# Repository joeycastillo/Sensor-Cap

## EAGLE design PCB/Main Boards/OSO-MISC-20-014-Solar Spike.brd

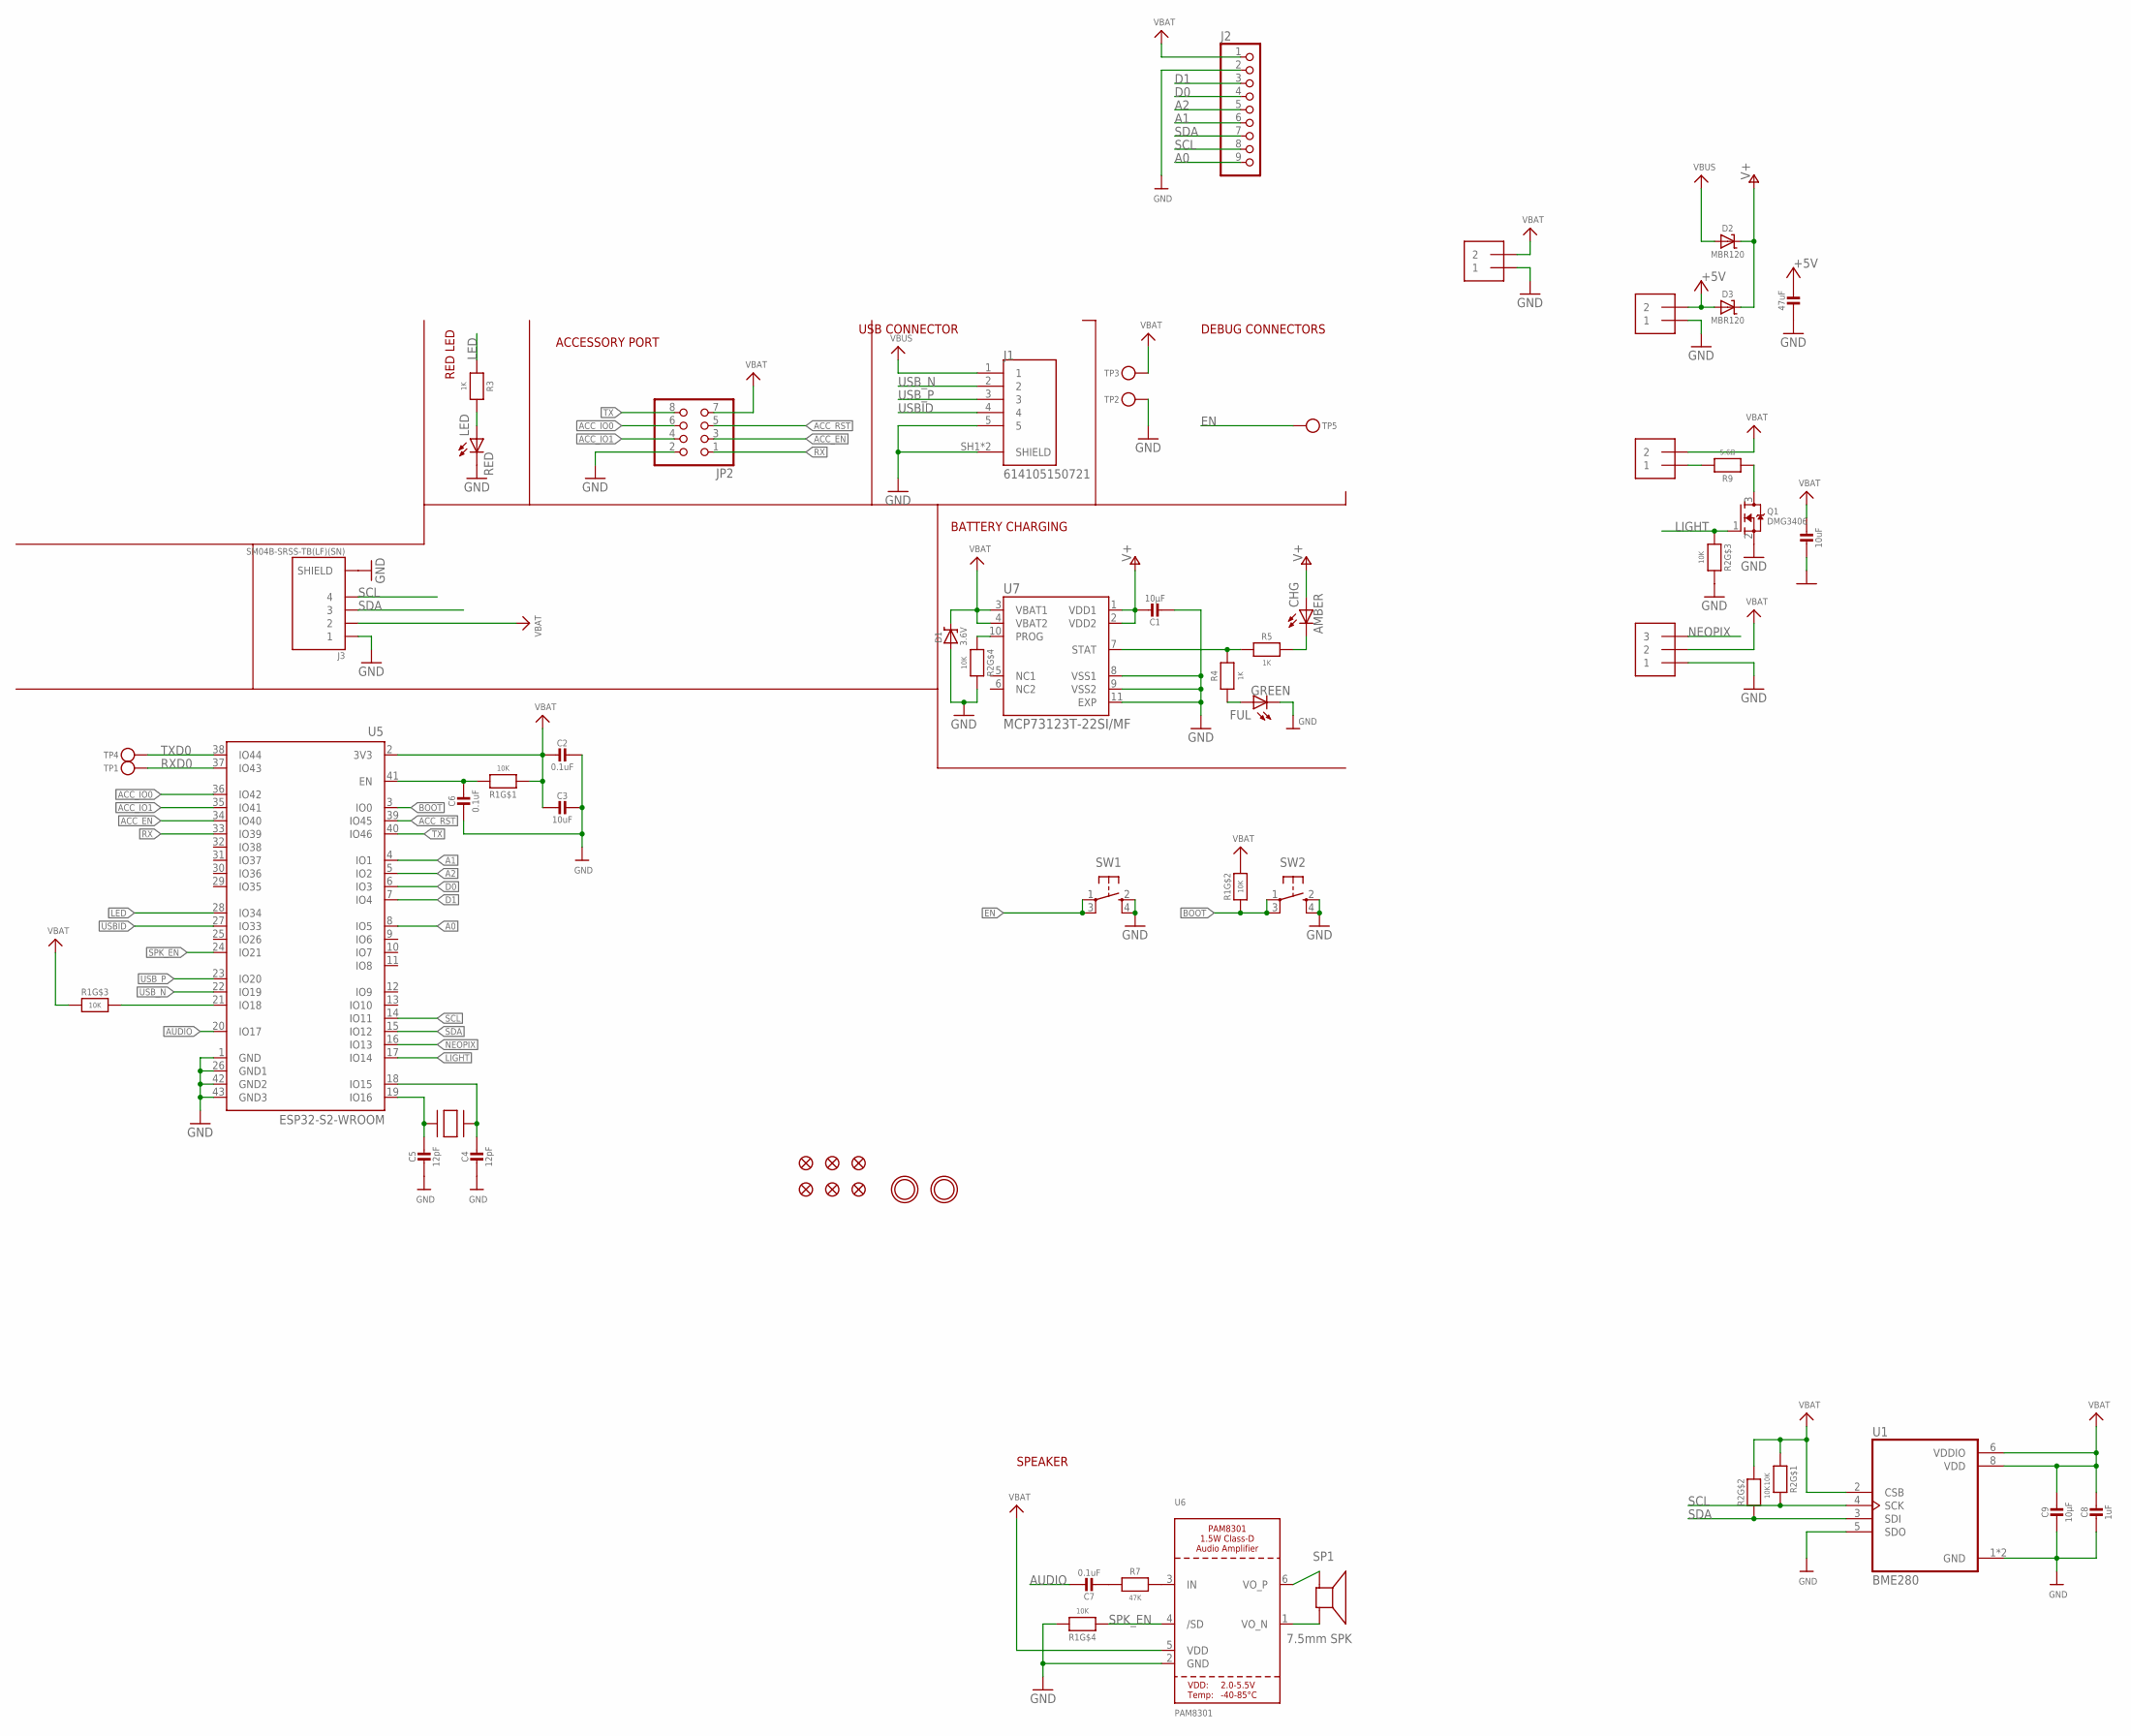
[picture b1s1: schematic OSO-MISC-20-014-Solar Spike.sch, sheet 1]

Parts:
BATTERY: 1X2-3.5MM
C1, C9: 10µF; 0805-NO
C2, C6, C7: 0.1uF; 0805-NO
C3, C10: 10uF; 0805-NO
C4, C5: 12pF; 0805-NO
C8: 1uF; 0805-NO
C11: 47uF; 0805-NO
CHG: AMBER; CHIPLED_0805
D1: 3.6V; SOD-123
D2, D3: MBR120; SOD-123
FID1, FID2, FID3, FID4, FID5, FID6: FIDUCIAL_1MM
FUL: GREEN; CHIPLED_0805
J1: 614105150721; WURTH_614105150721
J2: HEADER-1X9_JSTSH_VERT; JST_SH9_VERT
J3: SM04B-SRSS-TB(LF)(SN); JST_SM04B-SRSS-TB(LF)(SN)
JP2: PINHD-2X4SMT; PINHD_2X4_SMT
LED: RED; CHIPLED_0805
LIGHT: 1X2-3.5MM
NEOPIX: 1X3; 1X3-3.5MM
Q1: DMG3406; SOT23-WIDE
R1, R2: 10K; EXBV8V
R3, R4, R5: 1K; 0805-NO
R7: 47K; 0805-NO
R9: 5.6Ω; 0805-NO
SOLAR: 1X2-3.5MM
SP1: 7.5mm SPK; BUZZER_SMT_5MM
SW1, SW2: SPST_TACT-KMR2; KMR2
TP1, TP2, TP3, TP4, TP5: TESTPOINTROUND1.5MMNO; TESTPOINT_ROUND_1.5MM_NO
U1: BME280; PSON65P250X250X100-8N
U5: ESP32-S2-WROOM; MODULE_ESP32-S2-WROOM
U6: PAM8301; SOT23-6
U7: MCP73123T-22SI/MF; SON50P300X300X100-11N
U$1, U$4: MOUNTINGHOLE2.5; MOUNTINGHOLE_2.5_PLATED
X1: XTAL-3.2X1.5; XTAL3215

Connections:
+5V: C11.2, D3.A, SOLAR.2
A0: J2.9, U5.8 (IO5)
A1: J2.6, U5.4 (IO1)
A2: J2.5, U5.5 (IO2)
ACC_EN: JP2.3, U5.34 (IO40)
ACC_IO0: JP2.6, U5.36 (IO42)
ACC_IO1: JP2.4, U5.35 (IO41)
ACC_RST: JP2.5, U5.39 (IO45)
AUDIO: C7.1, U5.20 (IO17)
BOOT: R1.2 (1), SW2.1, SW2.3 (P1), U5.3 (IO0)
D0: J2.4, U5.6 (IO3)
D1: J2.3, U5.7 (IO4)
EN: C6.1, R1.8 (2), SW1.1, SW1.3 (P1), TP5.P$1, U5.41 (EN)
GND: BATTERY.1, C1.2, C2.1, C3.1, C4.2, C5.2, C6.2, C8.2, C9.2, C10.2, C11.1, D1.A, FUL.C, J1.5, J1.SH1 (SHIELD), J1.SH2 (SHIELD), J2.2, J3.1, J3.S1 (SHIELD), J3.S2 (SHIELD), JP2.2, LED.C, NEOPIX.1, Q1.2 (S), R1.5 (2), R2.5 (2), R2.6 (2), SOLAR.1, SW1.2 (S), SW1.4 (S1), SW2.2 (S), SW2.4 (S1), TP2.P$1, U1.1 (GND), U1.5 (SDO), U1.7 (GND), U5.1 (GND), U5.26 (GND1), U5.42 (GND2), U5.43 (GND3), U6.2 (GND), U7.8 (VSS1), U7.9 (VSS2), U7.11 (EXP)
LED: R3.1, U5.28 (IO34)
LIGHT: Q1.1 (G), R2.3 (1), U5.17 (IO14)
unnamed: R1.6 (2), U5.21 (IO18)
unnamed: LED.A, R3.2
unnamed: C7.2, R7.1
unnamed: R7.2, U6.3 (IN)
unnamed: CHG.C, R5.2
unnamed: FUL.A, R4.1
unnamed: Q1.3 (D), R9.1
unnamed: LIGHT.1, R9.2
NEOPIX: NEOPIX.3, U5.16 (IO13)
PROG: R2.4 (1), U7.10 (PROG)
RX: JP2.1, U5.33 (IO39)
RXD0: TP1.P$1, U5.37 (IO43)
SCL: J2.8, J3.4, R2.8 (2), U1.4 (SCK), U5.14 (IO11)
SDA: J2.7, J3.3, R2.7 (2), U1.3 (SDI), U5.15 (IO12)
SPK_EN: R1.4 (1), U5.24 (IO21), U6.4 (/SD)
SPK_N: SP1.+, U6.1 (VO_N)
SPK_P: SP1.-, U6.6 (VO_P)
STAT: R4.2, R5.1, U7.7 (STAT)
TX: JP2.8, U5.40 (IO46)
TXD0: TP4.P$1, U5.38 (IO44)
USBID: J1.4, U5.27 (IO33)
USB_N: J1.2, U5.22 (IO19)
USB_P: J1.3, U5.23 (IO20)
V+: C1.1, CHG.A, D2.C, D3.C, U7.1 (VDD1), U7.2 (VDD2)
VBAT: BATTERY.2, C2.2, C3.2, C8.1, C9.1, C10.1, D1.C, J2.1, J3.2, JP2.7, LIGHT.2, NEOPIX.2, R1.1, R1.3 (1), R1.7 (2), R2.1, R2.2 (1), TP3.P$1, U1.2 (CSB), U1.6 (VDDIO), U1.8 (VDD), U5.2 (3V3), U6.5 (VDD), U7.3 (VBAT1), U7.4 (VBAT2)
VBUS: D2.A, J1.1
XTAL_N: C5.1, U5.19 (IO16), X1.P$2
XTAL_P: C4.1, U5.18 (IO15), X1.P$1

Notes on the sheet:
BATTERY CHARGING
DEBUG CONNECTORS
USB CONNECTOR
RED LED
SPEAKER
ACCESSORY PORT

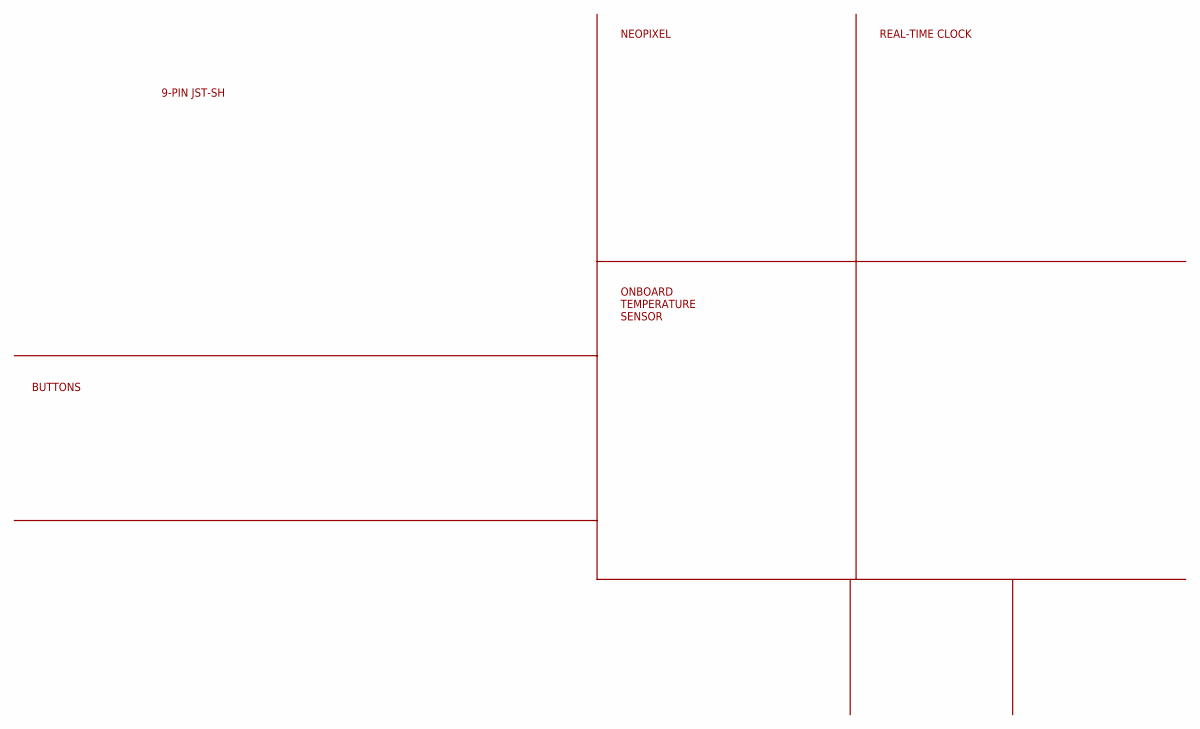
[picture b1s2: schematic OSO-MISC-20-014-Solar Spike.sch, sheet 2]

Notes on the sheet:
9-PIN JST-SH
ONBOARD TEMPERATURE SENSOR
BUTTONS
NEOPIXEL
REAL-TIME CLOCK

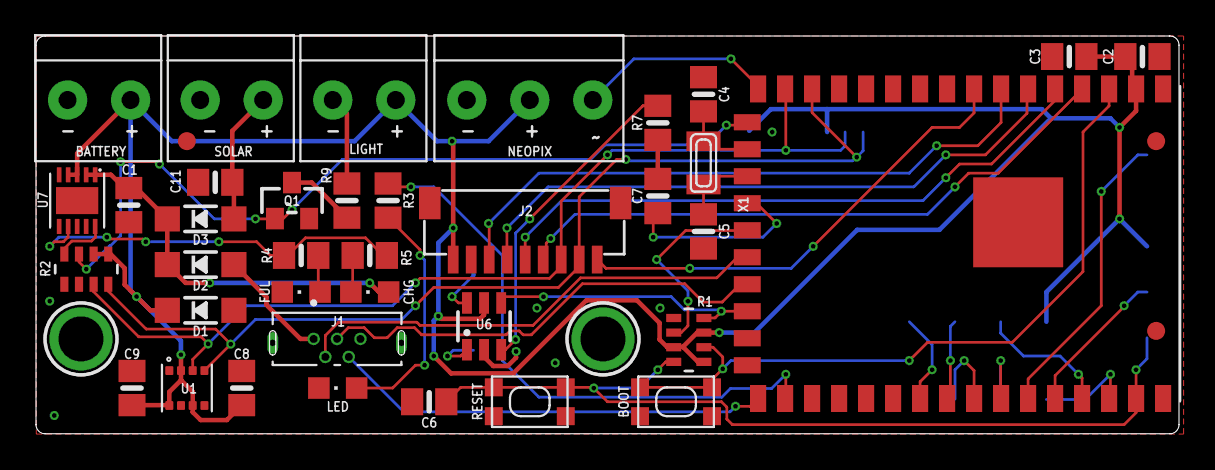
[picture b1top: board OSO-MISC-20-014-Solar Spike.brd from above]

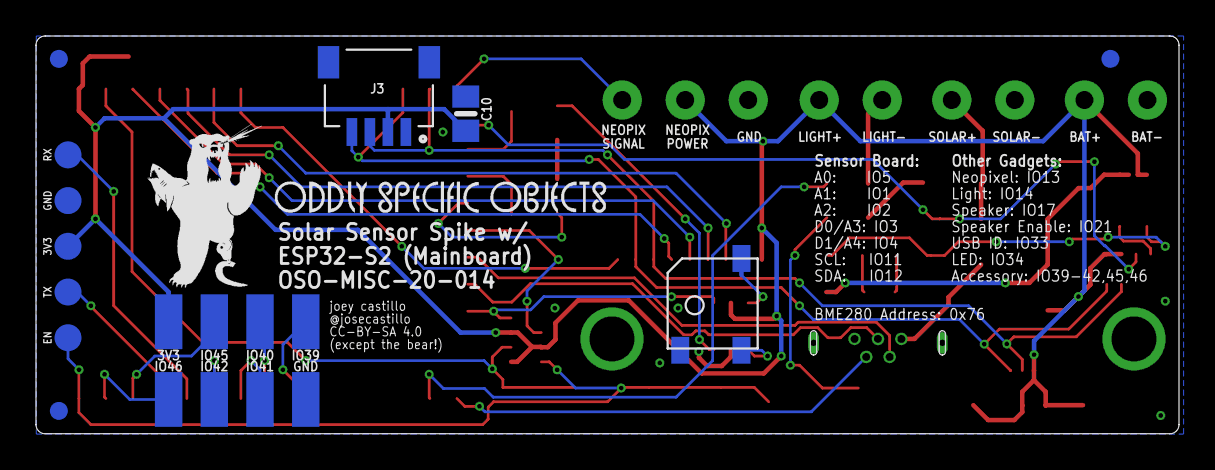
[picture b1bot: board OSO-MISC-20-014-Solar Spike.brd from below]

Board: 2 copper layers, 63.5 x 22.1 mm, 56 parts (14 on the bottom side), 44 nets.

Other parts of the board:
U$15: OSO_BEAR_250X360MIL_1000DPI
U$31: OSO_WORDMARK_ONELINE_725MIL_1000DPI

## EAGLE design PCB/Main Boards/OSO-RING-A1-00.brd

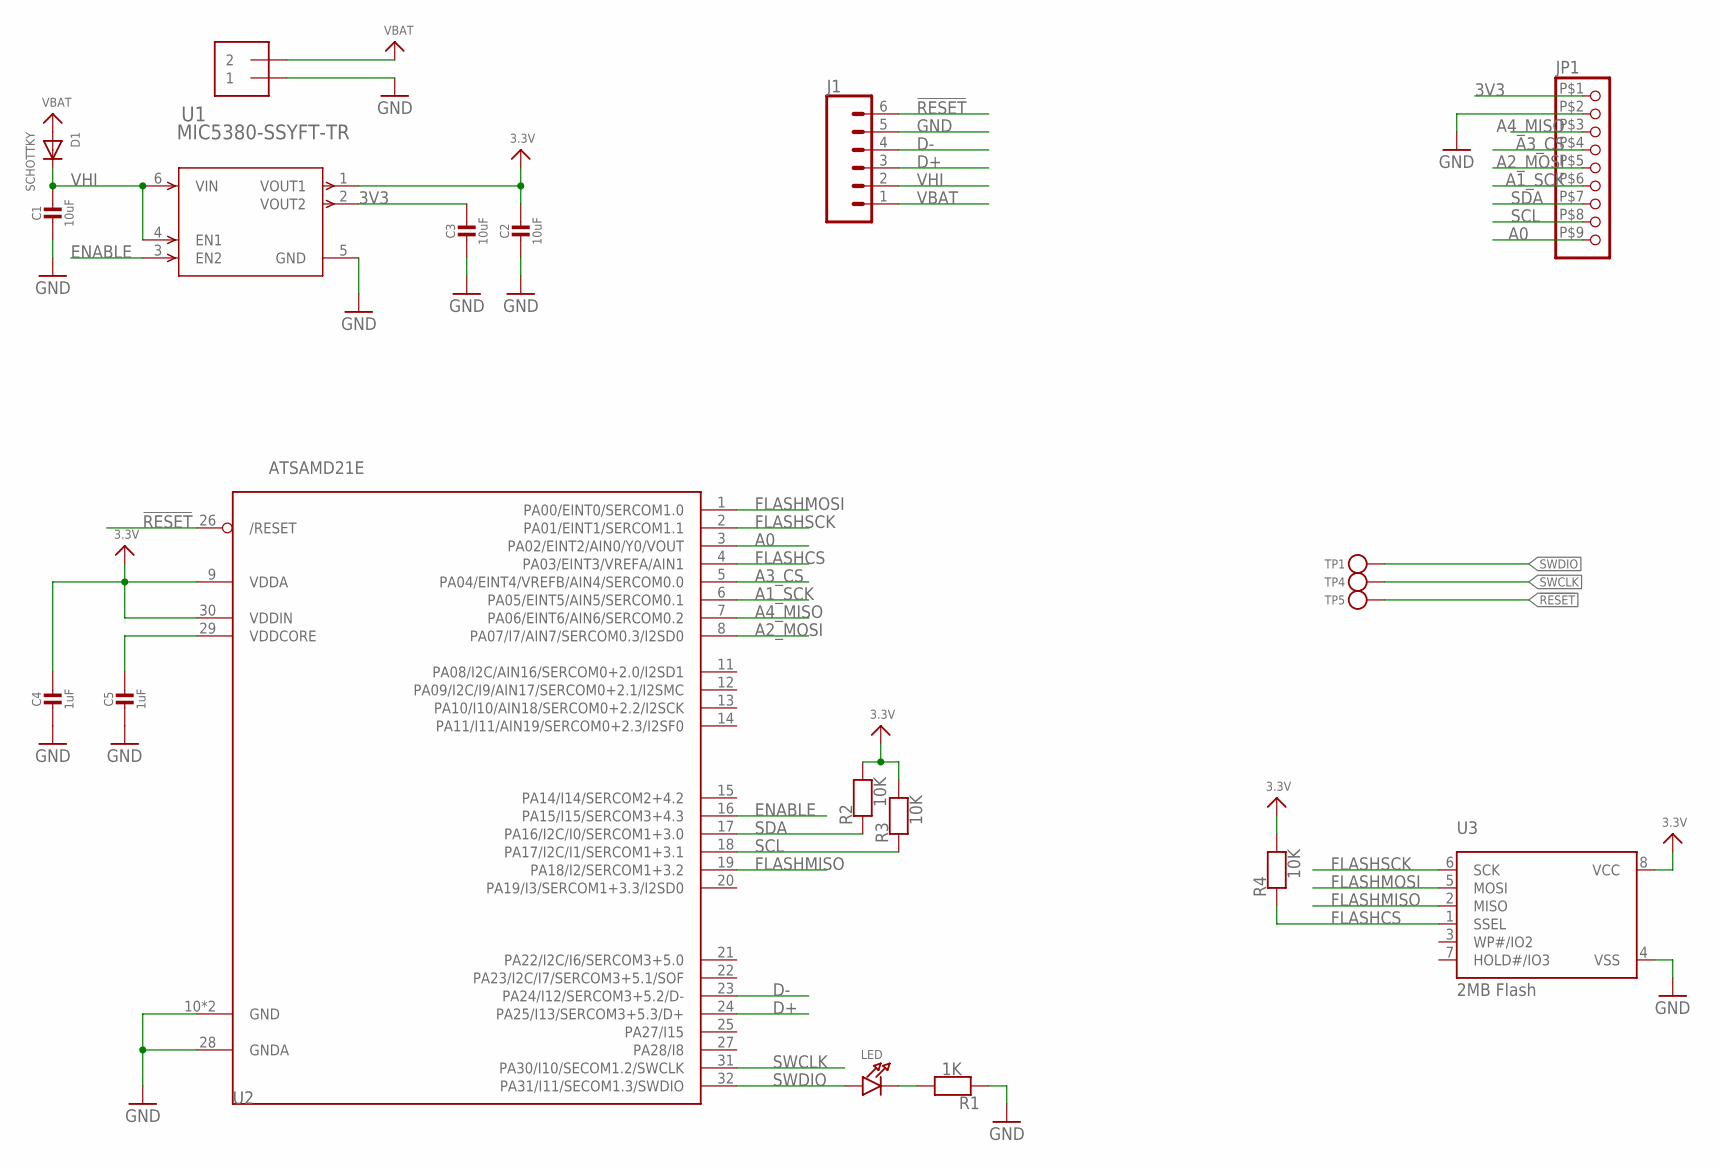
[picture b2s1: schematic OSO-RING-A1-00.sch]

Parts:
C1, C2, C3: 10uF; 0603-NO
C4, C5: 1uF; 0603-NO
D1: SCHOTTKY; SOD-123
J1: CONN_06SMD-1MM; 1X06-1MM
J2: 1X2SMT; 2PIN_SMT_CONNECTOR
JP1: HEADER-1X9BOARD_TO_FLEX; 9PIN_SMT_CONNECTOR
LED: LED0603_NOOUTLINE; CHIPLED_0603_NOOUTLINE
R1: 1K; 0603-NO
R2, R3, R4: 10K; 0603-NO
TP1, TP4, TP5: TESTPOINTROUND1.5MMNO; TESTPOINT_ROUND_1.5MM_NO
U1: MIC5380-SSYFT-TR; TMLF-6_FT_MCH
U2: ATSAMD21E; QFN32_5MM
U3: 2MB Flash; USON8

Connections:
3.3V: C2.1, C4.1, R2.2, R3.2, R4.2, U1.1 (VOUT1), U2.9 (VDDA), U2.30 (VDDIN), U3.8 (VCC)
3V3: C3.1, JP1.P$1 (1), U1.2 (VOUT2)
!RESET: J1.6, TP5.P$1, U2.26 (/RESET)
A0: JP1.P$9 (9), U2.3 (PA02/EINT2/AIN0/Y0/VOUT)
A1_SCK: JP1.P$6 (6), U2.6 (PA05/EINT5/AIN5/SERCOM0.1)
A2_MOSI: JP1.P$5 (5), U2.8 (PA07/I7/AIN7/SERCOM0.3/I2SD0)
A3_CS: JP1.P$4 (4), U2.5 (PA04/EINT4/VREFB/AIN4/SERCOM0.0)
A4_MISO: JP1.P$3 (3), U2.7 (PA06/EINT6/AIN6/SERCOM0.2)
D+: J1.3, U2.24 (PA25/I13/SERCOM3+5.3/D+)
D-: J1.4, U2.23 (PA24/I12/SERCOM3+5.2/D-)
ENABLE: U1.3 (EN2), U2.16 (PA15/I15/SERCOM3+4.3)
FLASHCS: R4.1, U2.4 (PA03/EINT3/VREFA/AIN1), U3.1 (SSEL)
FLASHMISO: U2.19 (PA18/I2/SERCOM1+3.2), U3.2 (MISO)
FLASHMOSI: U2.1 (PA00/EINT0/SERCOM1.0), U3.5 (MOSI)
FLASHSCK: U2.2 (PA01/EINT1/SERCOM1.1), U3.6 (SCK)
GND: C1.2, C2.2, C3.2, C4.2, C5.2, J1.5, J2.P$1 (1), JP1.P$2 (2), R1.1, U1.5 (GND), U2.10 (GND), U2.28 (GNDA), U2.33 (GND), U3.4 (VSS)
unnamed: LED.C, R1.2
SCL: JP1.P$8 (8), R3.1, U2.18 (PA17/I2C/I1/SERCOM1+3.1)
SDA: JP1.P$7 (7), R2.1, U2.17 (PA16/I2C/I0/SERCOM1+3.0)
SWCLK: TP4.P$1, U2.31 (PA30/I10/SECOM1.2/SWCLK)
SWDIO: LED.A, TP1.P$1, U2.32 (PA31/I11/SECOM1.3/SWDIO)
VBAT: D1.A, J1.1, J2.P$2 (2)
VDDCORE: C5.1, U2.29 (VDDCORE)
VHI: C1.1, D1.C, J1.2, U1.4 (EN1), U1.6 (VIN)

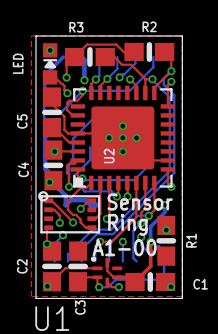
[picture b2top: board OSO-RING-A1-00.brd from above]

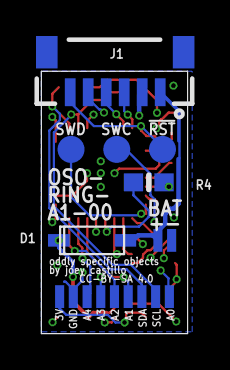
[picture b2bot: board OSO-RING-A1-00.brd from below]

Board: 4 copper layers, 8.1 x 14.6 mm, 20 parts (8 on the bottom side), 24 nets.

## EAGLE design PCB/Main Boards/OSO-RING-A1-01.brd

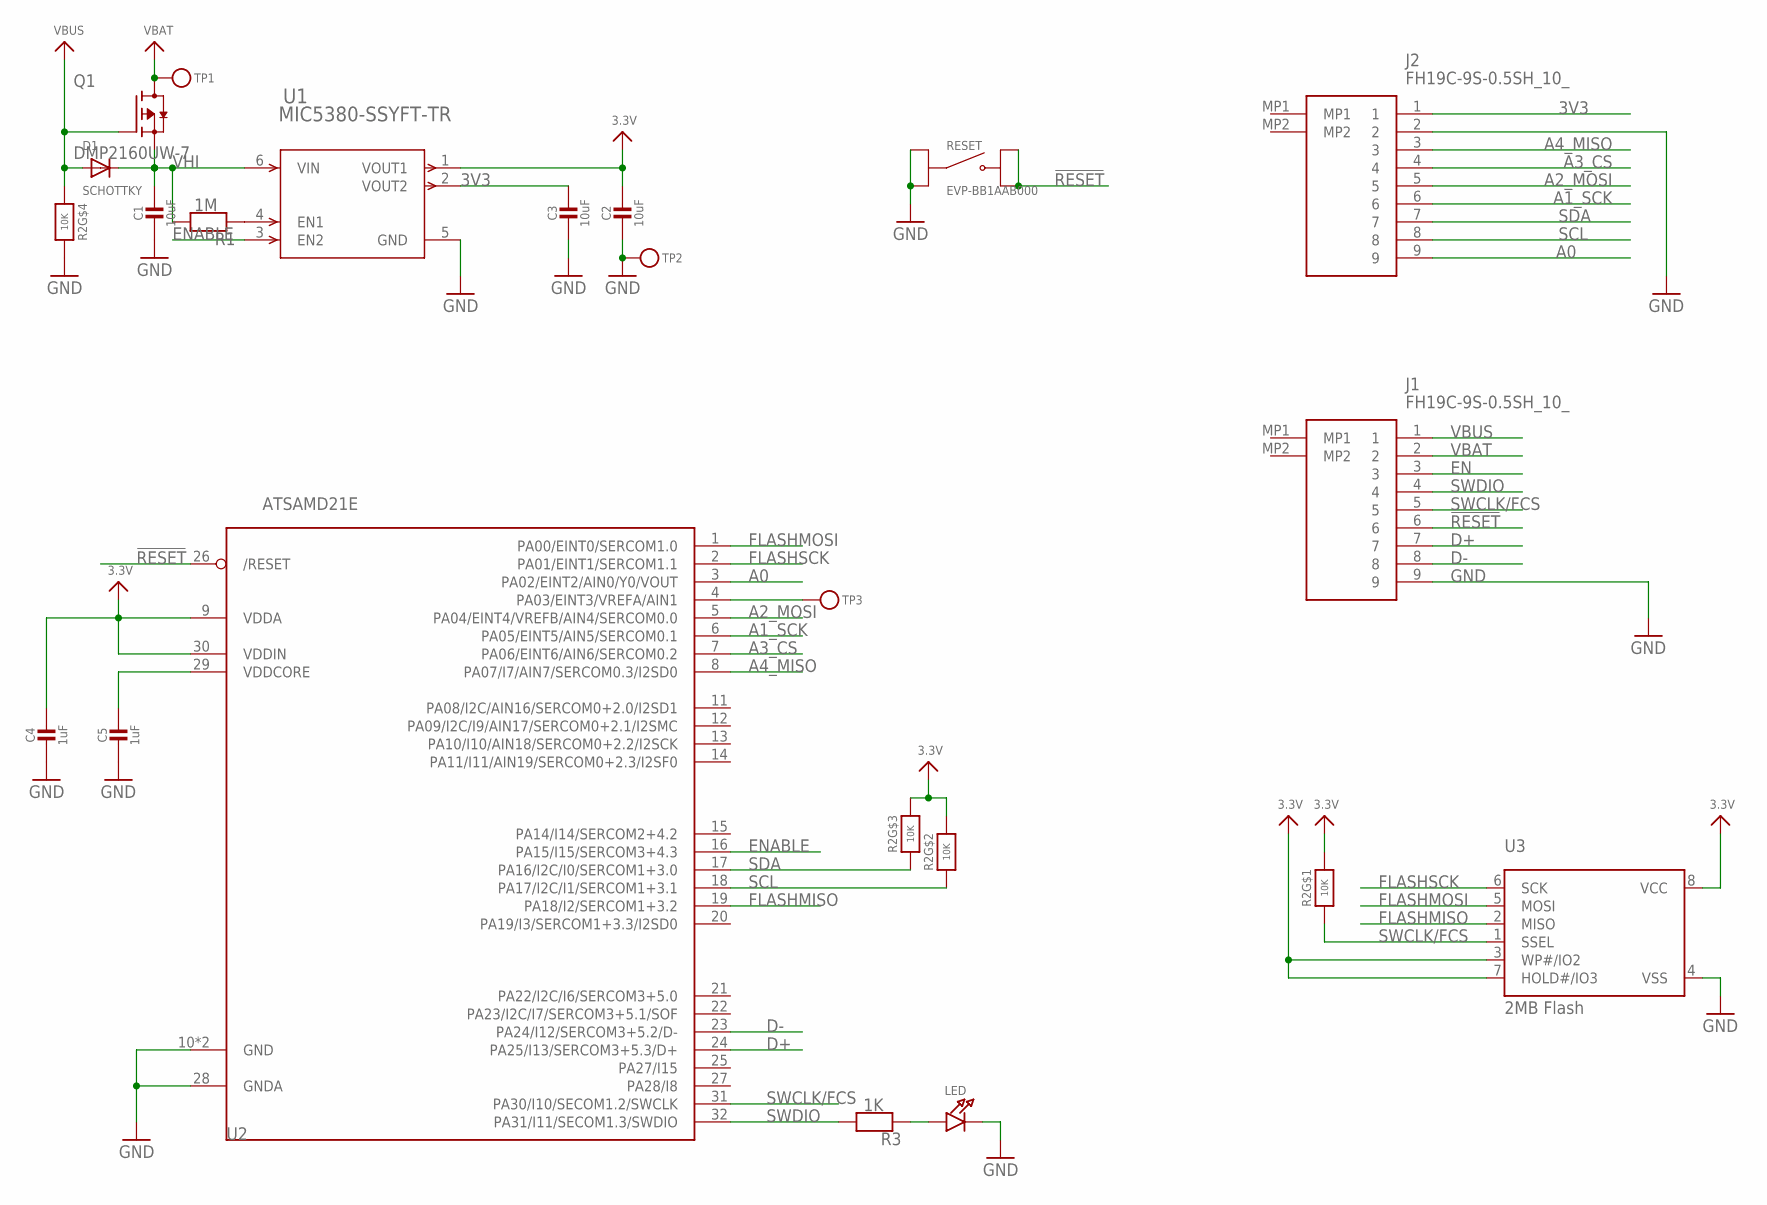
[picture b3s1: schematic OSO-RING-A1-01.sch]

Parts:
C1, C2, C3: 10uF; _0603MP
C4, C5: 1uF; _0603MP
D1: SCHOTTKY; SOD-323F
J1, J2: FH19C-9S-0.5SH_10_; FH19C9S05SH10
LED: LED0603_NOOUTLINE; CHIPLED_0603_NOOUTLINE
Q1: DMP2160UW-7; SOT65P210X110-3N
R1: 1M; _0603MP
R2: 10K; EXBV8V
R3: 1K; _0603MP
RESET: EVP-BB1AAB000; SW_EVP-BB1AAB000
TP1, TP2: TESTPOINTPAD2MM; TESTPOINT_PAD_2MM
TP3: TESTPOINTPAD1MM; TESTPOINT_PAD_1MM
U1: MIC5380-SSYFT-TR; TMLF-6_FT_MCH
U2: ATSAMD21E; QFN32_5MM
U3: 2MB Flash; USON8

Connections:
3.3V: C2.1, C4.1, R2.6 (2), R2.7 (2), R2.8 (2), U1.1 (VOUT1), U2.9 (VDDA), U2.30 (VDDIN), U3.3 (WP#/IO2), U3.7 (HOLD#/IO3), U3.8 (VCC)
3V3: C3.1, J2.1, U1.2 (VOUT2)
!RESET: J1.6, RESET.B1, RESET.B2, U2.26 (/RESET)
A0: J2.9, U2.3 (PA02/EINT2/AIN0/Y0/VOUT)
A1_SCK: J2.6, U2.6 (PA05/EINT5/AIN5/SERCOM0.1)
A2_MOSI: J2.5, U2.5 (PA04/EINT4/VREFB/AIN4/SERCOM0.0)
A3_CS: J2.4, U2.7 (PA06/EINT6/AIN6/SERCOM0.2)
A4_MISO: J2.3, U2.8 (PA07/I7/AIN7/SERCOM0.3/I2SD0)
D+: J1.7, U2.24 (PA25/I13/SERCOM3+5.3/D+)
D-: J1.8, U2.23 (PA24/I12/SERCOM3+5.2/D-)
EN: J1.3, R1.1, U1.4 (EN1)
ENABLE: U1.3 (EN2), U2.16 (PA15/I15/SERCOM3+4.3)
FLASHMISO: U2.19 (PA18/I2/SERCOM1+3.2), U3.2 (MISO)
FLASHMOSI: U2.1 (PA00/EINT0/SERCOM1.0), U3.5 (MOSI)
FLASHSCK: U2.2 (PA01/EINT1/SERCOM1.1), U3.6 (SCK)
FREE_PIN!: TP3.P$1, U2.4 (PA03/EINT3/VREFA/AIN1)
GND: C1.2, C2.2, C3.2, C4.2, C5.2, J1.9, J2.2, LED.C, R2.5 (2), RESET.A1, RESET.A2, TP2.P$1, U1.5 (GND), U2.10 (GND), U2.28 (GNDA), U2.33 (GND), U3.4 (VSS)
unnamed: LED.A, R3.1
SCL: J2.8, R2.2 (1), U2.18 (PA17/I2C/I1/SERCOM1+3.1)
SDA: J2.7, R2.3 (1), U2.17 (PA16/I2C/I0/SERCOM1+3.0)
SWCLK/FCS: J1.5, R2.1, U2.31 (PA30/I10/SECOM1.2/SWCLK), U3.1 (SSEL)
SWDIO: J1.4, R3.2, U2.32 (PA31/I11/SECOM1.3/SWDIO)
VBAT: J1.2, Q1.3 (D), TP1.P$1
VBUS: D1.A, J1.1, Q1.1 (G), R2.4 (1)
VDDCORE: C5.1, U2.29 (VDDCORE)
VHI: C1.1, D1.C, Q1.2 (S), R1.2, U1.6 (VIN)

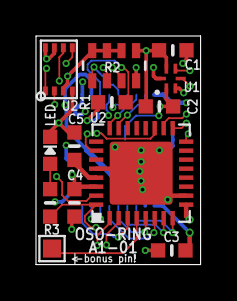
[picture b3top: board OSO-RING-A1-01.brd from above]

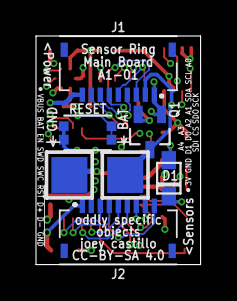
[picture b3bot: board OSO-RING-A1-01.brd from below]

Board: 6 copper layers, 9.1 x 12.7 mm, 20 parts (7 on the bottom side), 26 nets.

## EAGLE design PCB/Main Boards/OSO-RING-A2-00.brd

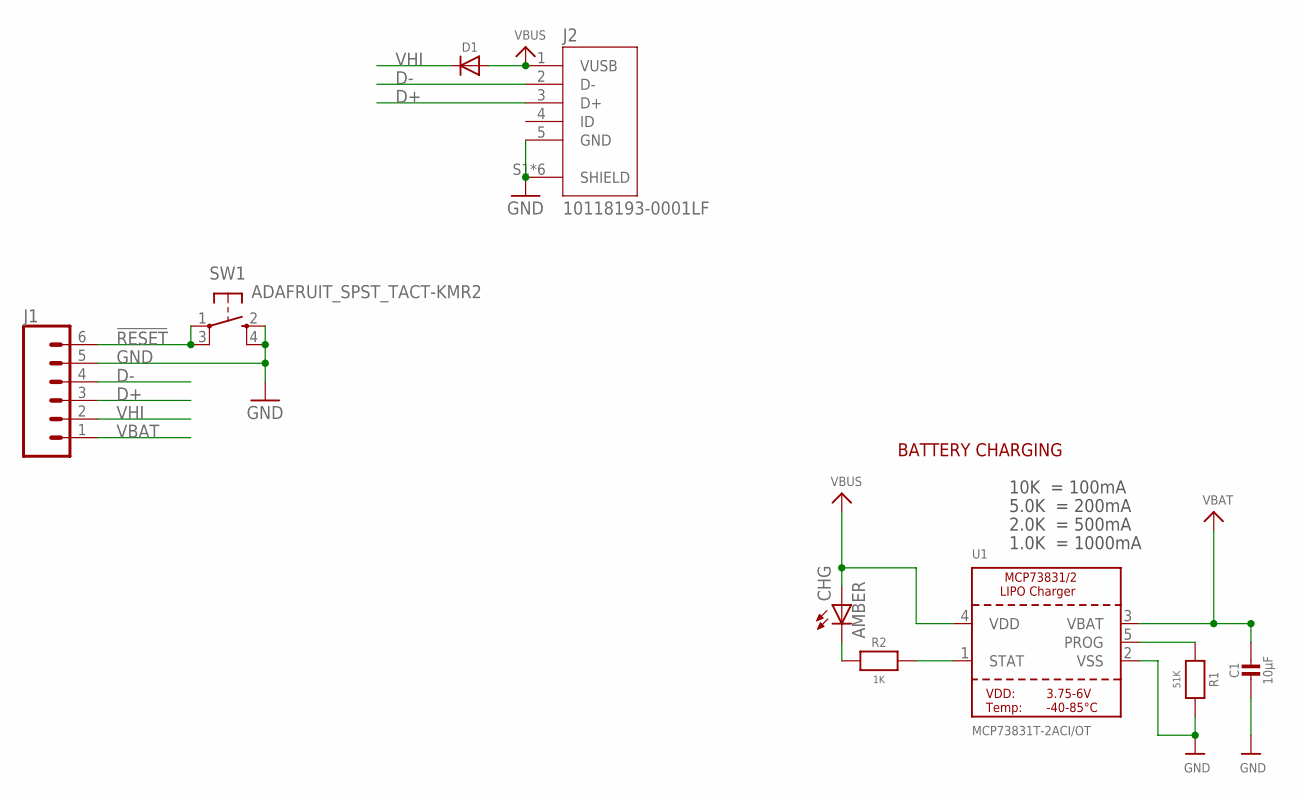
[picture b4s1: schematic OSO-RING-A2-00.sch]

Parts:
C1: 10µF; 0805-NO
CHG: AMBER; CHIPLED_0805
D1: MICROBUILDER_DIODESOD-123; MICROBUILDER_SOD-123
J1: CONN_06SMD-1MM; 1X06-1MM
J2: 10118193-0001LF; FCI_10118193-0001LF
R1: 51K; 0805-NO
R2: 1K; 0805-NO
SW1: ADAFRUIT_SPST_TACT-KMR2; ADAFRUIT_KMR2
U1: MCP73831T-2ACI/OT; SOT23-5

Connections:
!RESET: J1.6, SW1.1, SW1.3 (P1)
D+: J1.3, J2.3 (D+)
D-: J1.4, J2.2 (D-)
GND: C1.2, J1.5, J2.5 (GND), J2.S1 (SHIELD), J2.S2 (SHIELD), J2.S3 (SHIELD), J2.S4 (SHIELD), J2.S5 (SHIELD), J2.S6 (SHIELD), R1.2, SW1.2 (S), SW1.4 (S1), U1.2 (VSS)
unnamed: CHG.C, R2.1
PROG: R1.1, U1.5 (PROG)
STAT: R2.2, U1.1 (STAT)
VBAT: C1.1, J1.1, U1.3 (VBAT)
VBUS: CHG.A, D1.A, J2.1 (VUSB), U1.4 (VDD)
VHI: D1.C, J1.2

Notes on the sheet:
10K = 100mA
5.0K = 200mA
2.0K = 500mA
1.0K = 1000mA
BATTERY CHARGING

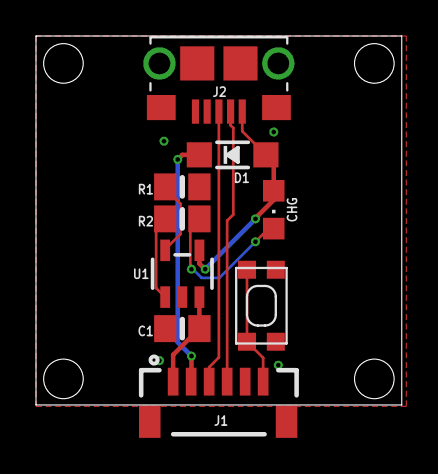
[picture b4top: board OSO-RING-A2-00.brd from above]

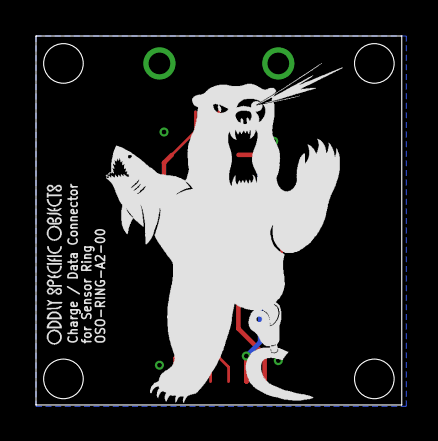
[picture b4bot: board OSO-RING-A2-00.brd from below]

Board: 2 copper layers, 20.3 x 20.5 mm, 11 parts (2 on the bottom side), 10 nets.

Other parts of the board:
U$2: OSO_BEAR_525X750MIL_1000DPI
U$3: OSO_WORDMARK_ONELINE_350MIL_1000DPI

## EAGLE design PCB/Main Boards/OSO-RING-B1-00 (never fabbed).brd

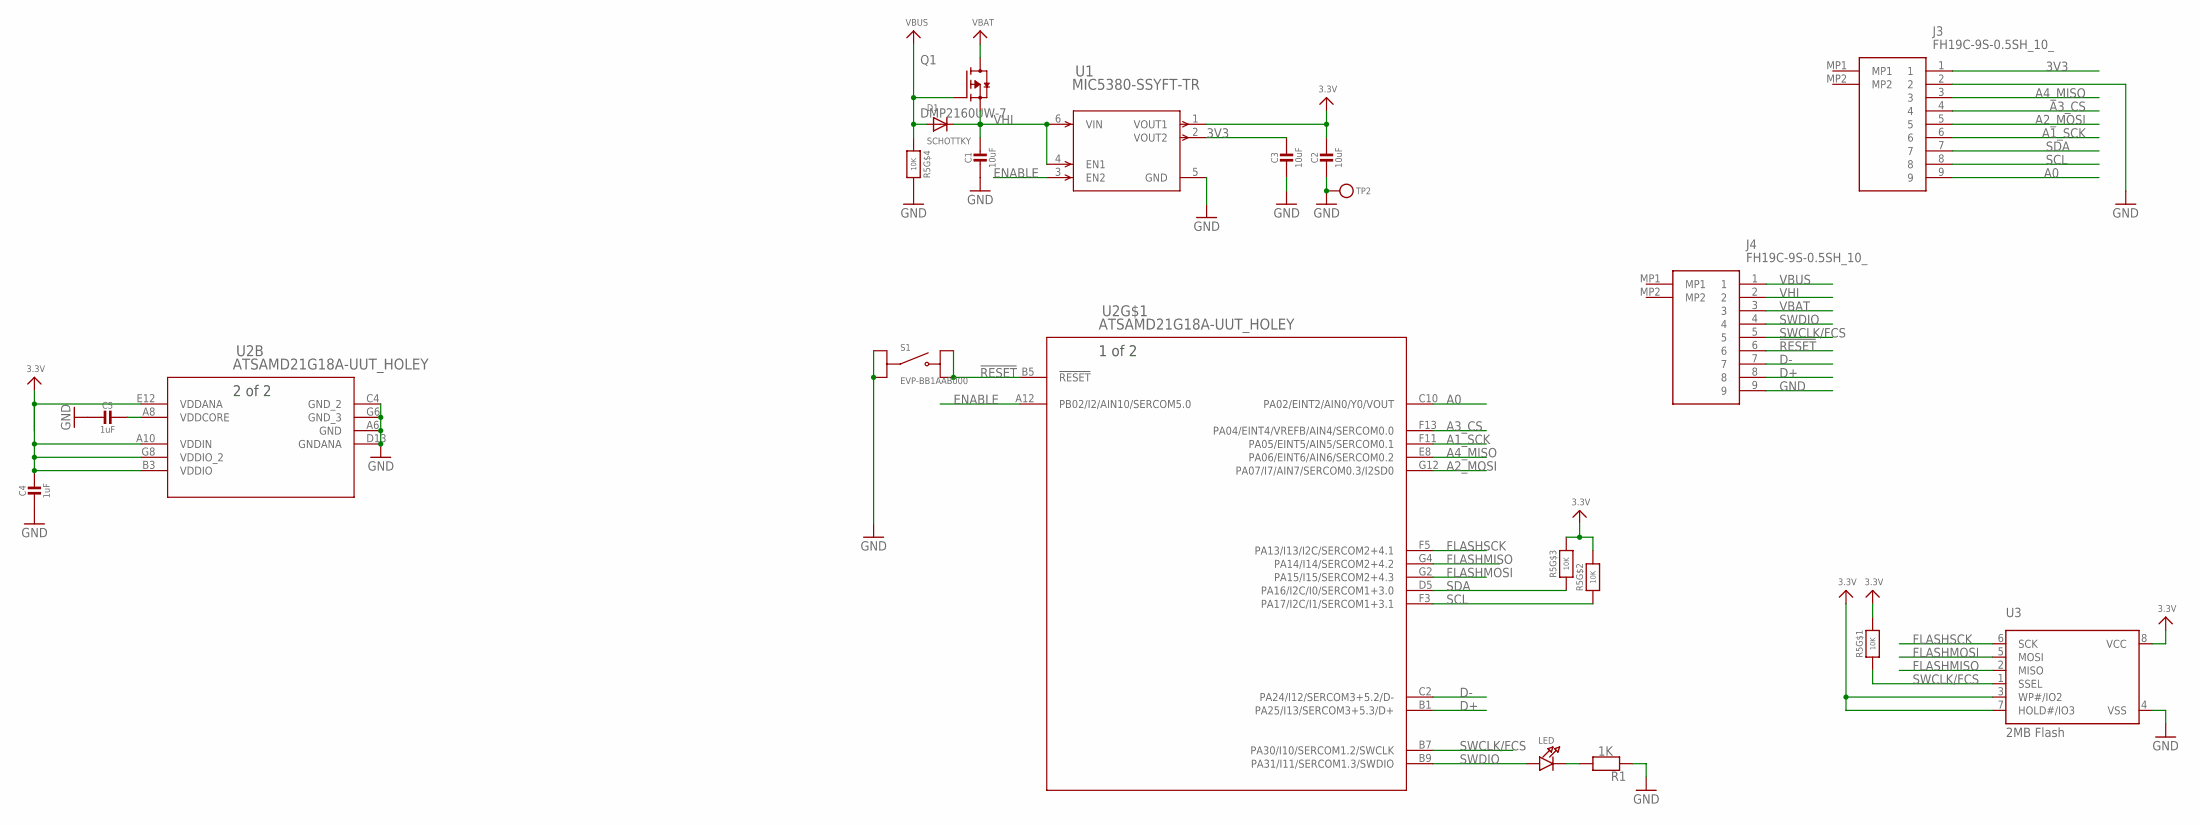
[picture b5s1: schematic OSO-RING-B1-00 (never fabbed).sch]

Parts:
C1, C2, C3: 10uF; _0603MP
C4, C5: 1uF; _0603MP
D1: SCHOTTKY; SOD-323F
J3, J4: FH19C-9S-0.5SH_10_; FH19C9S05SH10
LED: LED0603_NOOUTLINE; CHIPLED_0603_NOOUTLINE
Q1: DMP2160UW-7; SOT65P210X110-3N
R1: 1K; _0603MP
R5: 10K; EXBV8V
S1: EVP-BB1AAB000; SW_EVP-BB1AAB000
TP2: TESTPOINTPAD1MM; TESTPOINT_PAD_1MM
U1: MIC5380-SSYFT-TR; TMLF-6_FT_MCH
U2: ATSAMD21G18A-UUT_HOLEY; WLCSP45_2P6X2P9_HOLEY
U3: 2MB Flash; USON8

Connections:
3.3V: C2.1, C4.1, R5.6 (2), R5.7 (2), R5.8 (2), U1.1 (VOUT1), U2.A10 (VDDIN), U2.B3 (VDDIO), U2.E12 (VDDANA), U2.G8 (VDDIO_2), U3.3 (WP#/IO2), U3.7 (HOLD#/IO3), U3.8 (VCC)
3V3: C3.1, J3.1, U1.2 (VOUT2)
!RESET: J4.6, S1.B1, S1.B2, U2.B5 (!RESET)
A0: J3.9, U2.C10 (PA02/EINT2/AIN0/Y0/VOUT)
A1_SCK: J3.6, U2.F11 (PA05/EINT5/AIN5/SERCOM0.1)
A2_MOSI: J3.5, U2.G12 (PA07/I7/AIN7/SERCOM0.3/I2SD0)
A3_CS: J3.4, U2.F13 (PA04/EINT4/VREFB/AIN4/SERCOM0.0)
A4_MISO: J3.3, U2.E8 (PA06/EINT6/AIN6/SERCOM0.2)
D+: J4.8, U2.B1 (PA25/I13/SERCOM3+5.3/D+)
D-: J4.7, U2.C2 (PA24/I12/SERCOM3+5.2/D-)
ENABLE: U1.3 (EN2), U2.A12 (PB02/I2/AIN10/SERCOM5.0)
FLASHMISO: U2.G4 (PA14/I14/SERCOM2+4.2), U3.2 (MISO)
FLASHMOSI: U2.G2 (PA15/I15/SERCOM2+4.3), U3.5 (MOSI)
FLASHSCK: U2.F5 (PA13/I13/I2C/SERCOM2+4.1), U3.6 (SCK)
GND: C1.2, C2.2, C3.2, C4.2, C5.2, J3.2, J4.9, R1.1, R5.5 (2), S1.A1, S1.A2, TP2.P$1, U1.5 (GND), U2.A6 (GND), U2.C4 (GND_2), U2.D13 (GNDANA), U2.G6 (GND_3), U3.4 (VSS)
unnamed: LED.C, R1.2
SCL: J3.8, R5.2 (1), U2.F3 (PA17/I2C/I1/SERCOM1+3.1)
SDA: J3.7, R5.3 (1), U2.D5 (PA16/I2C/I0/SERCOM1+3.0)
SWCLK/FCS: J4.5, R5.1, U2.B7 (PA30/I10/SERCOM1.2/SWCLK), U3.1 (SSEL)
SWDIO: J4.4, LED.A, U2.B9 (PA31/I11/SERCOM1.3/SWDIO)
VBAT: J4.3, Q1.3 (D)
VBUS: D1.A, J4.1, Q1.1 (G), R5.4 (1)
VDDCORE: C5.1, U2.A8 (VDDCORE)
VHI: C1.1, D1.C, J4.2, Q1.2 (S), U1.4 (EN1), U1.6 (VIN)

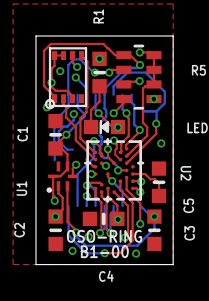
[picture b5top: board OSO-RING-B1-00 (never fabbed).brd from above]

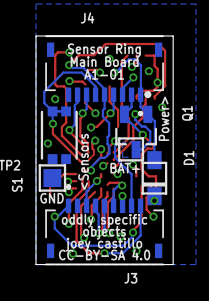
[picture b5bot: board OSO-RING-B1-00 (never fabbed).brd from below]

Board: 4 copper layers, 7.6 x 12.7 mm, 17 parts (6 on the bottom side), 24 nets.

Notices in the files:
PCB/Main Boards/OSO-MISC-20-014-Solar Spike.brd:
CC-BY-SA 4.0
parts and their libraries:
microbuilder: This work is placed in the public domain, and may be freely used for commercial and non-commercial work with the following conditions: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
SparkFun-Connectors: Licensing: Creative Commons ShareAlike 4.0 International - https://creativecommons.org/licenses/by-sa/4.0
